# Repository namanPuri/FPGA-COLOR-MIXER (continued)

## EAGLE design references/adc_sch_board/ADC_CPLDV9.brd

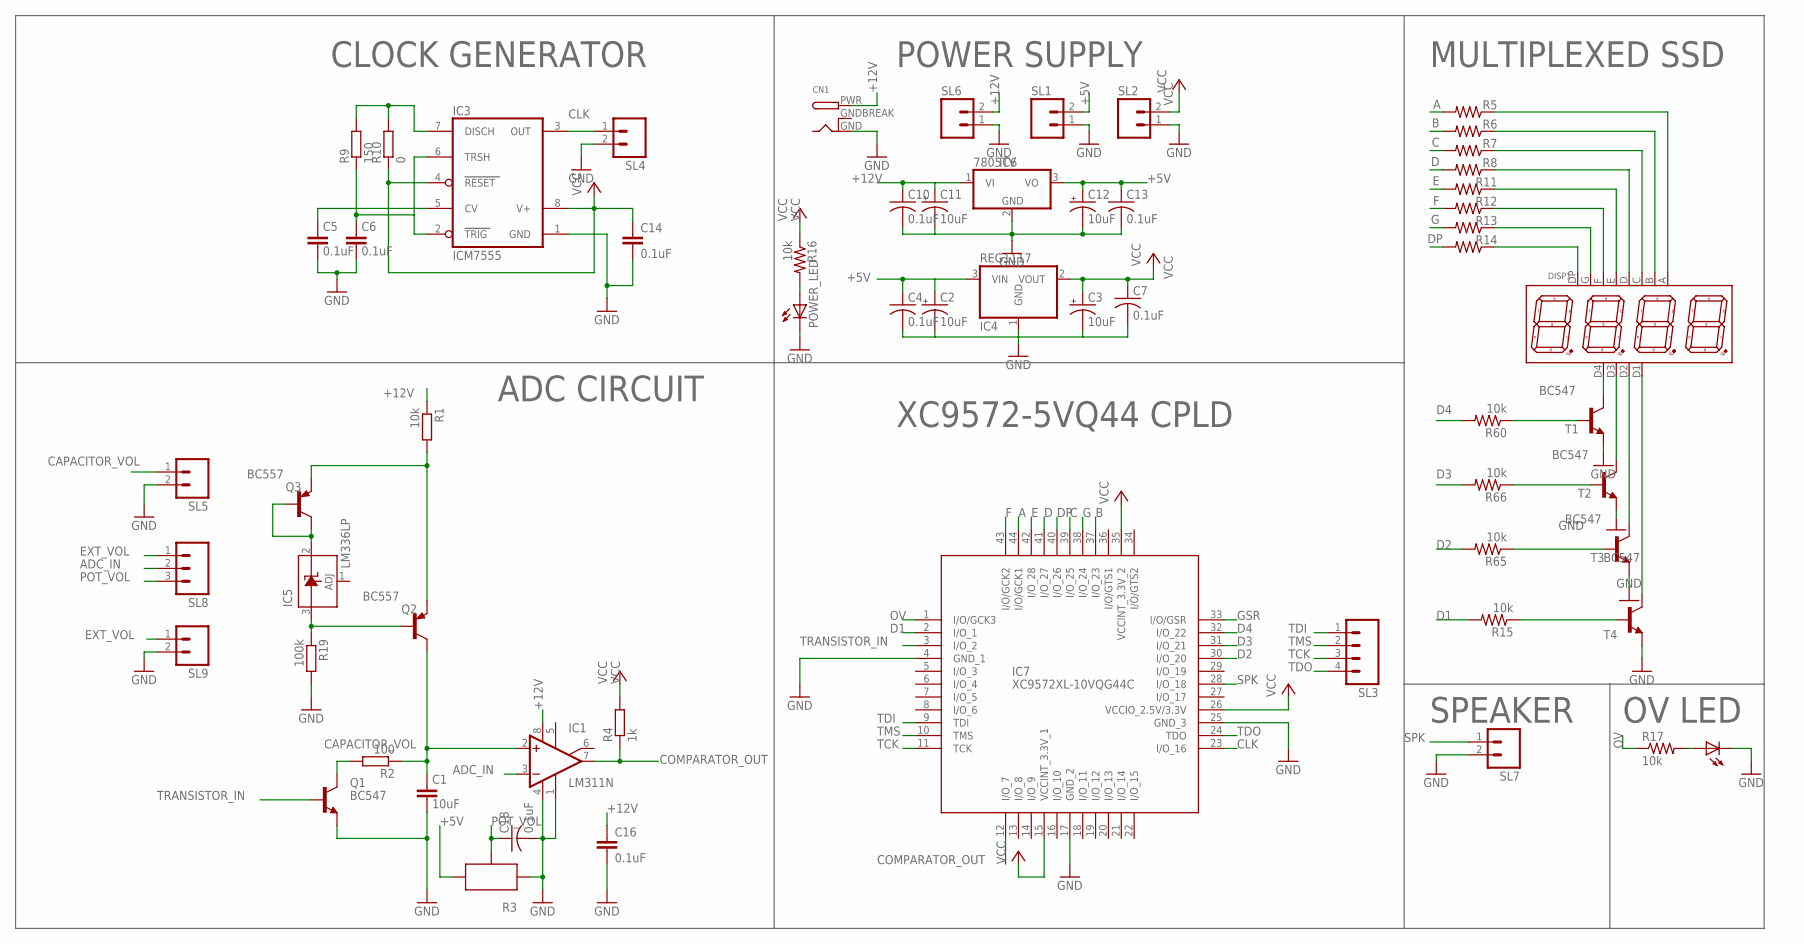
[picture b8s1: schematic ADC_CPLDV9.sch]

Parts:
C1: 10uF; C025-025X050
C2, C3, C11, C12: 10uF; B/3528-21R
C4, C7, C10, C13, C18: 0.1uF; C0805
C5, C6: 0.1uF; C025-024X044
C14, C16: 0.1uF; C025-025X050
CN1: DCBARRELPTH; DCJACK_2MM_PTH
DISP1: 7-SEG_4D_0.36; 7SEG-4DIG
IC1: LM311N; DIL08
IC3: ICM7555; DIL08
IC4: REG1117; SOT223
IC5: LM336LP; TO92
IC6: 7805TV; TO220V
IC7: XC9572XL-10VQG44C; 44_PIN_BOB
POWER_LED, POWER_LED1: LED3MM
Q1: BC547; TO92
Q2, Q3: BC557; TO92
R1: 10k; 0204/7
R2: 100; 0204/7
R3: POTNORMAL; RJ9W
R4: 1k; 0207/10
R5, R6, R7, R11, R12, R13, R14: 330; 0207/7
R8: 1k; 0207/7
R9: 150; 0204/7
R10: 0; 0204/7
R15, R16, R17, R60, R65, R66: 10k; 0207/7
R19: 100k; 0204/7
SL1, SL2, SL4, SL5, SL6, SL7, SL9: M02; 02P
SL3: M04; 04P
SL8: M03; 03P
T1, T2, T3, T4: BC547; TO92

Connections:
+5V: C2.+, C4.1, C12.+, C13.1, IC4.3 (VIN), IC6.3 (VO), R3.A, SL1.2
+12V: C10.1, C11.+, C16.1, CN1.PWR, IC1.8 (V+), IC6.1 (VI), R1.1, SL6.2
A: IC7.44 (I/O/GCK1), R5.2
ADC_IN: IC1.3 (-IN), SL8.2
B: IC7.37 (I/O_23), R6.2
C: IC7.39 (I/O_25), R7.2
CAPACITOR_VOL: C1.1, IC1.2 (+IN), Q2.3 (C), R2.1, SL5.1
CLK: IC3.3 (OUT), IC7.23 (I/O_16), SL4.1
COMPARATOR_OUT: IC1.7 (OUT), IC7.12 (I/O_7), R4.1
D: IC7.41 (I/O_27), R8.2
D1: IC7.2 (I/O_1), R15.2
D2: IC7.30 (I/O_20), R65.2
D3: IC7.31 (I/O_21), R66.2
D4: IC7.32 (I/O_22), R60.2
DP: IC7.40 (I/O_26), R14.2
E: IC7.42 (I/O_28), R11.2
EXT_VOL: SL8.1, SL9.1
F: IC7.43 (I/O/GCK2), R12.2
G: IC7.38 (I/O_24), R13.2
GND: C1.2, C2.-, C3.-, C4.2, C5.2, C6.2, C7.2, C10.2, C11.-, C12.-, C13.2, C14.2, C16.2, C18.2, CN1.GND, IC1.1 (GND), IC1.4 (V-), IC3.1 (GND), IC4.1 (GND), IC6.2 (GND), IC7.4 (GND_1), IC7.17 (GND_2), IC7.25 (GND_3), POWER_LED.K (C), POWER_LED1.K (C), Q1.1 (E), R3.E, R19.2, SL1.1, SL2.1, SL4.2, SL5.2, SL6.1, SL7.2, SL9.2, T1.1 (E), T2.1 (E), T3.1 (E), T4.1 (E)
GNDBREAK: CN1.GNDBREAK
GSR: IC7.33 (I/O/GSR)
unnamed: C6.1, IC3.2 (TRIG), IC3.6 (TRSH), R9.1
unnamed: IC5.3 (A), Q2.2 (B), R19.1
unnamed: Q1.3 (C), R2.2
unnamed: POWER_LED1.A, R17.2
unnamed: IC3.7 (DISCH), R9.2, R10.2
unnamed: C5.1, IC3.5 (CV)
unnamed: DISP1.D3, T2.3 (C)
unnamed: DISP1.D2, T3.3 (C)
unnamed: DISP1.D1, T4.3 (C)
unnamed: POWER_LED.A, R16.2
unnamed: DISP1.DP, R14.1
unnamed: DISP1.G, R13.1
unnamed: DISP1.F, R12.1
unnamed: DISP1.E, R11.1
unnamed: DISP1.D, R8.1
unnamed: DISP1.C, R7.1
unnamed: DISP1.B, R6.1
unnamed: DISP1.A, R5.1
unnamed: IC5.2 (C), Q3.2 (B), Q3.3 (C)
unnamed: Q2.1 (E), Q3.1 (E), R1.2
unnamed: DISP1.D4, T1.3 (C)
unnamed: R60.1, T1.2 (B)
unnamed: R66.1, T2.2 (B)
unnamed: R65.1, T3.2 (B)
unnamed: R15.1, T4.2 (B)
OV: IC7.1 (I/O/GCK3), R17.1
POT_VOL: C18.1, R3.S, SL8.3
SPK: IC7.28 (I/O_18), SL7.1
TCK: IC7.11 (TCK), SL3.3
TDI: IC7.9 (TDI), SL3.1
TDO: IC7.24 (TDO), SL3.4
TMS: IC7.10 (TMS), SL3.2
TRANSISTOR_IN: IC7.3 (I/O_2), Q1.2 (B)
VCC: C3.+, C7.1, C14.1, IC3.4 (RESET), IC3.8 (V+), IC4.2 (VOUT), IC7.15 (VCCINT_3.3V_1), IC7.26 (VCCIO_2.5V/3.3V), IC7.35 (VCCINT_3.3V_2), R4.2, R10.1, R16.1, SL2.2

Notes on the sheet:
MULTIPLEXED SSD
POWER SUPPLY
ADC CIRCUIT
CLOCK GENERATOR
XC9572-5VQ44 CPLD
SPEAKER
OV LED

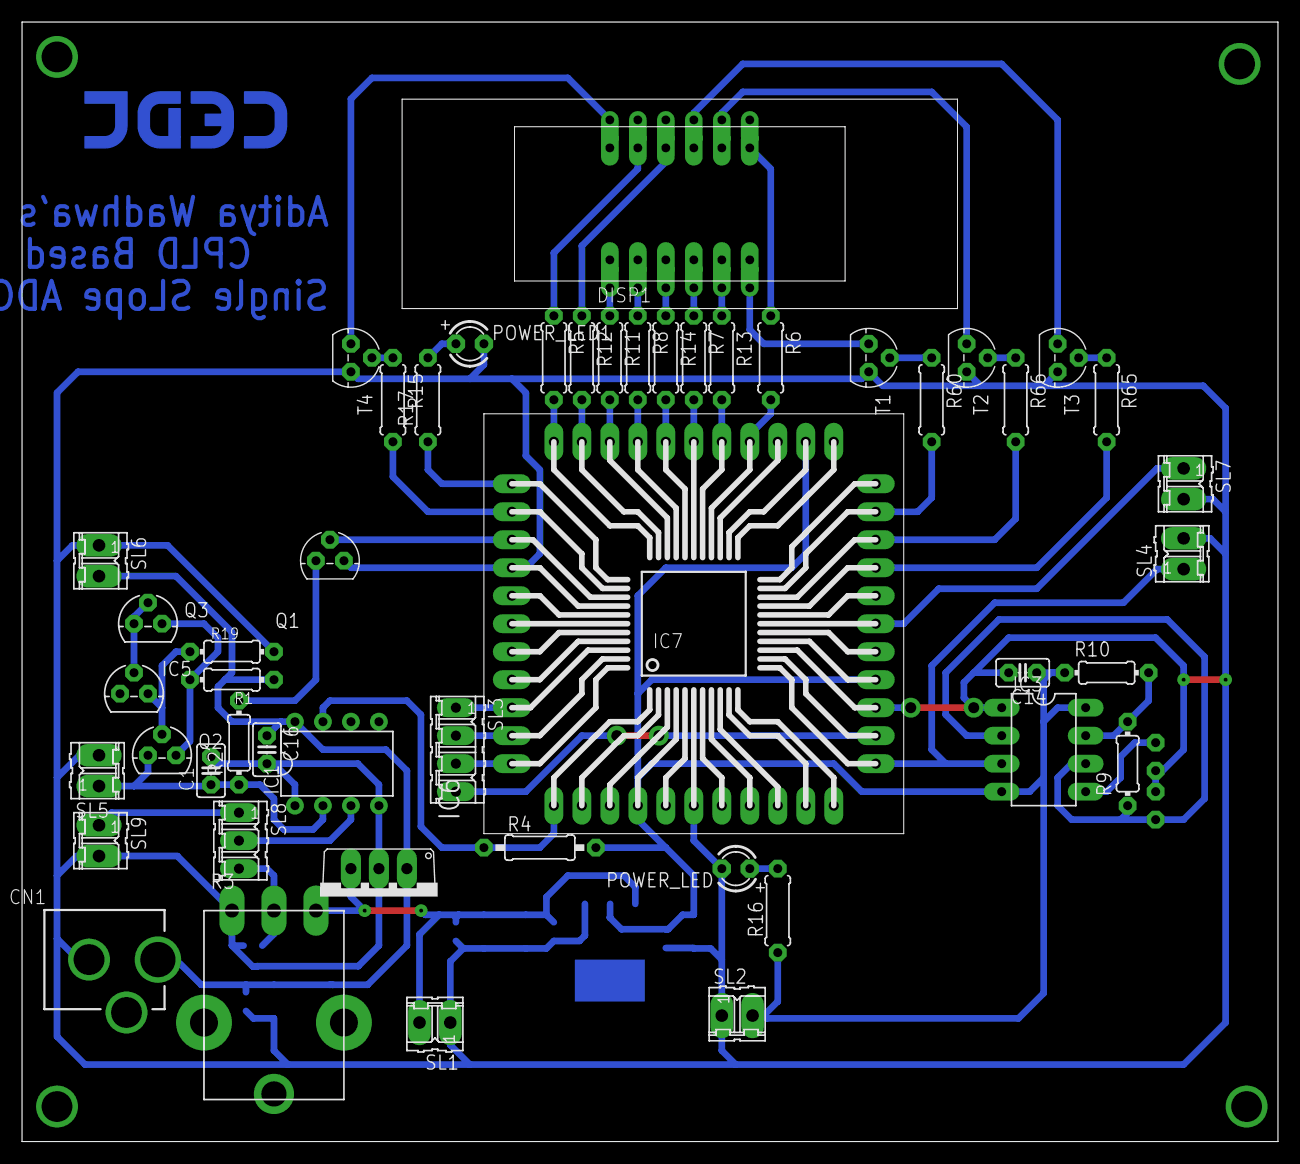
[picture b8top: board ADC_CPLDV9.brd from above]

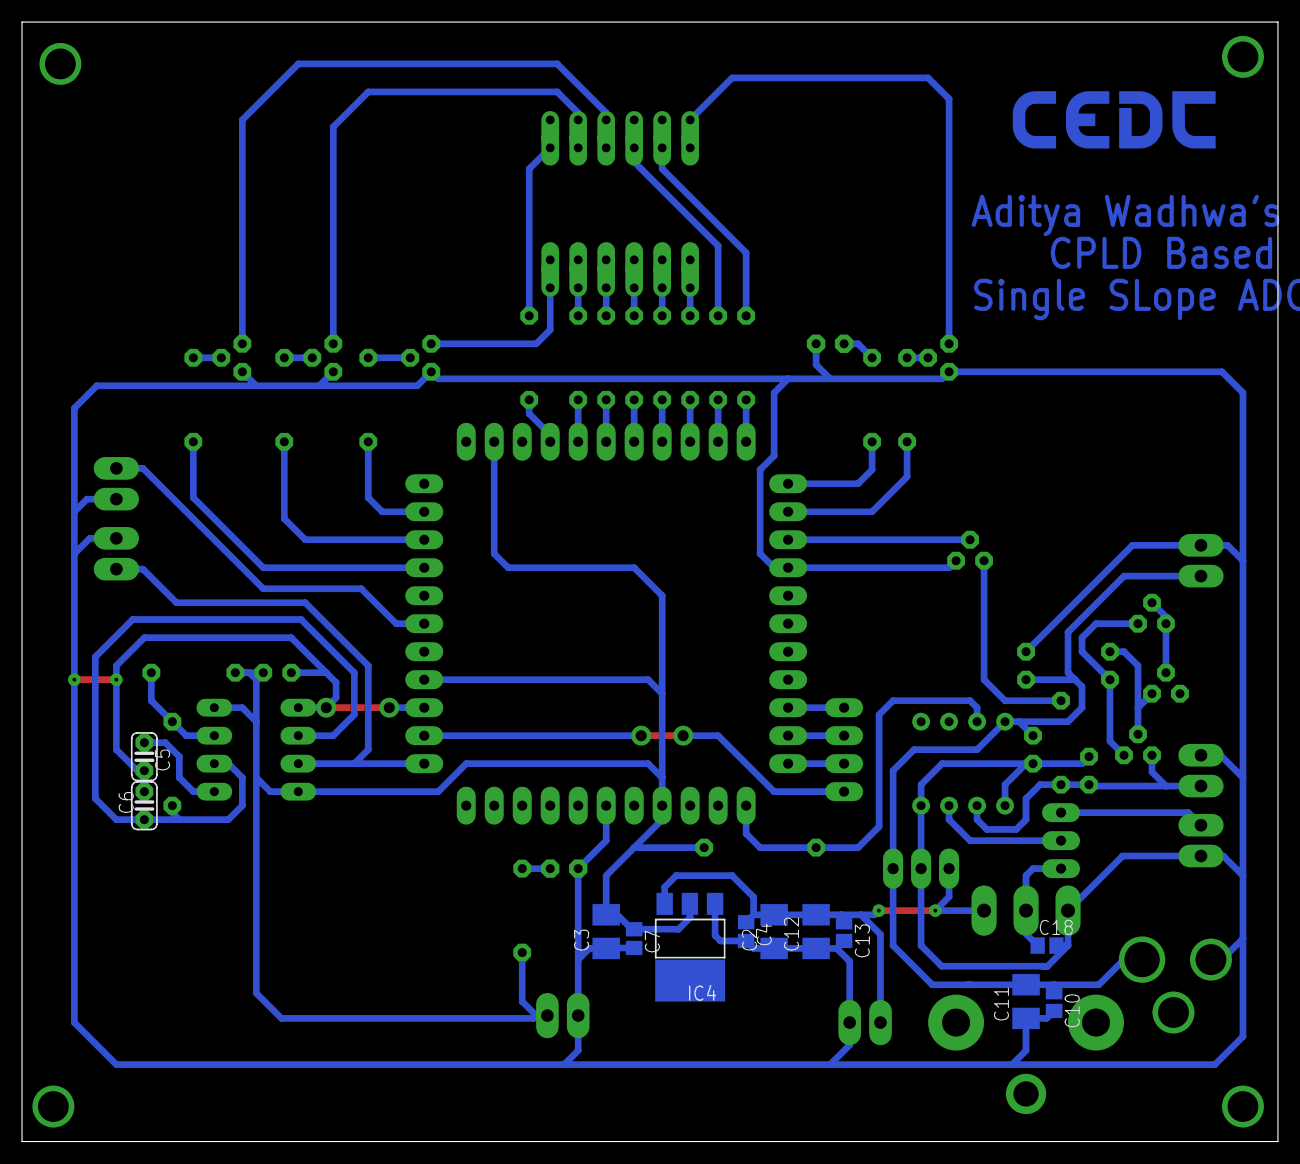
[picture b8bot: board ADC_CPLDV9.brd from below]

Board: 2 copper layers, 114.0 x 101.6 mm, 62 parts (12 on the bottom side), 54 nets.

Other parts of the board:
U$1: LOGO-CEDT-BOT-18MM

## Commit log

2023-02-01 flushed latest
